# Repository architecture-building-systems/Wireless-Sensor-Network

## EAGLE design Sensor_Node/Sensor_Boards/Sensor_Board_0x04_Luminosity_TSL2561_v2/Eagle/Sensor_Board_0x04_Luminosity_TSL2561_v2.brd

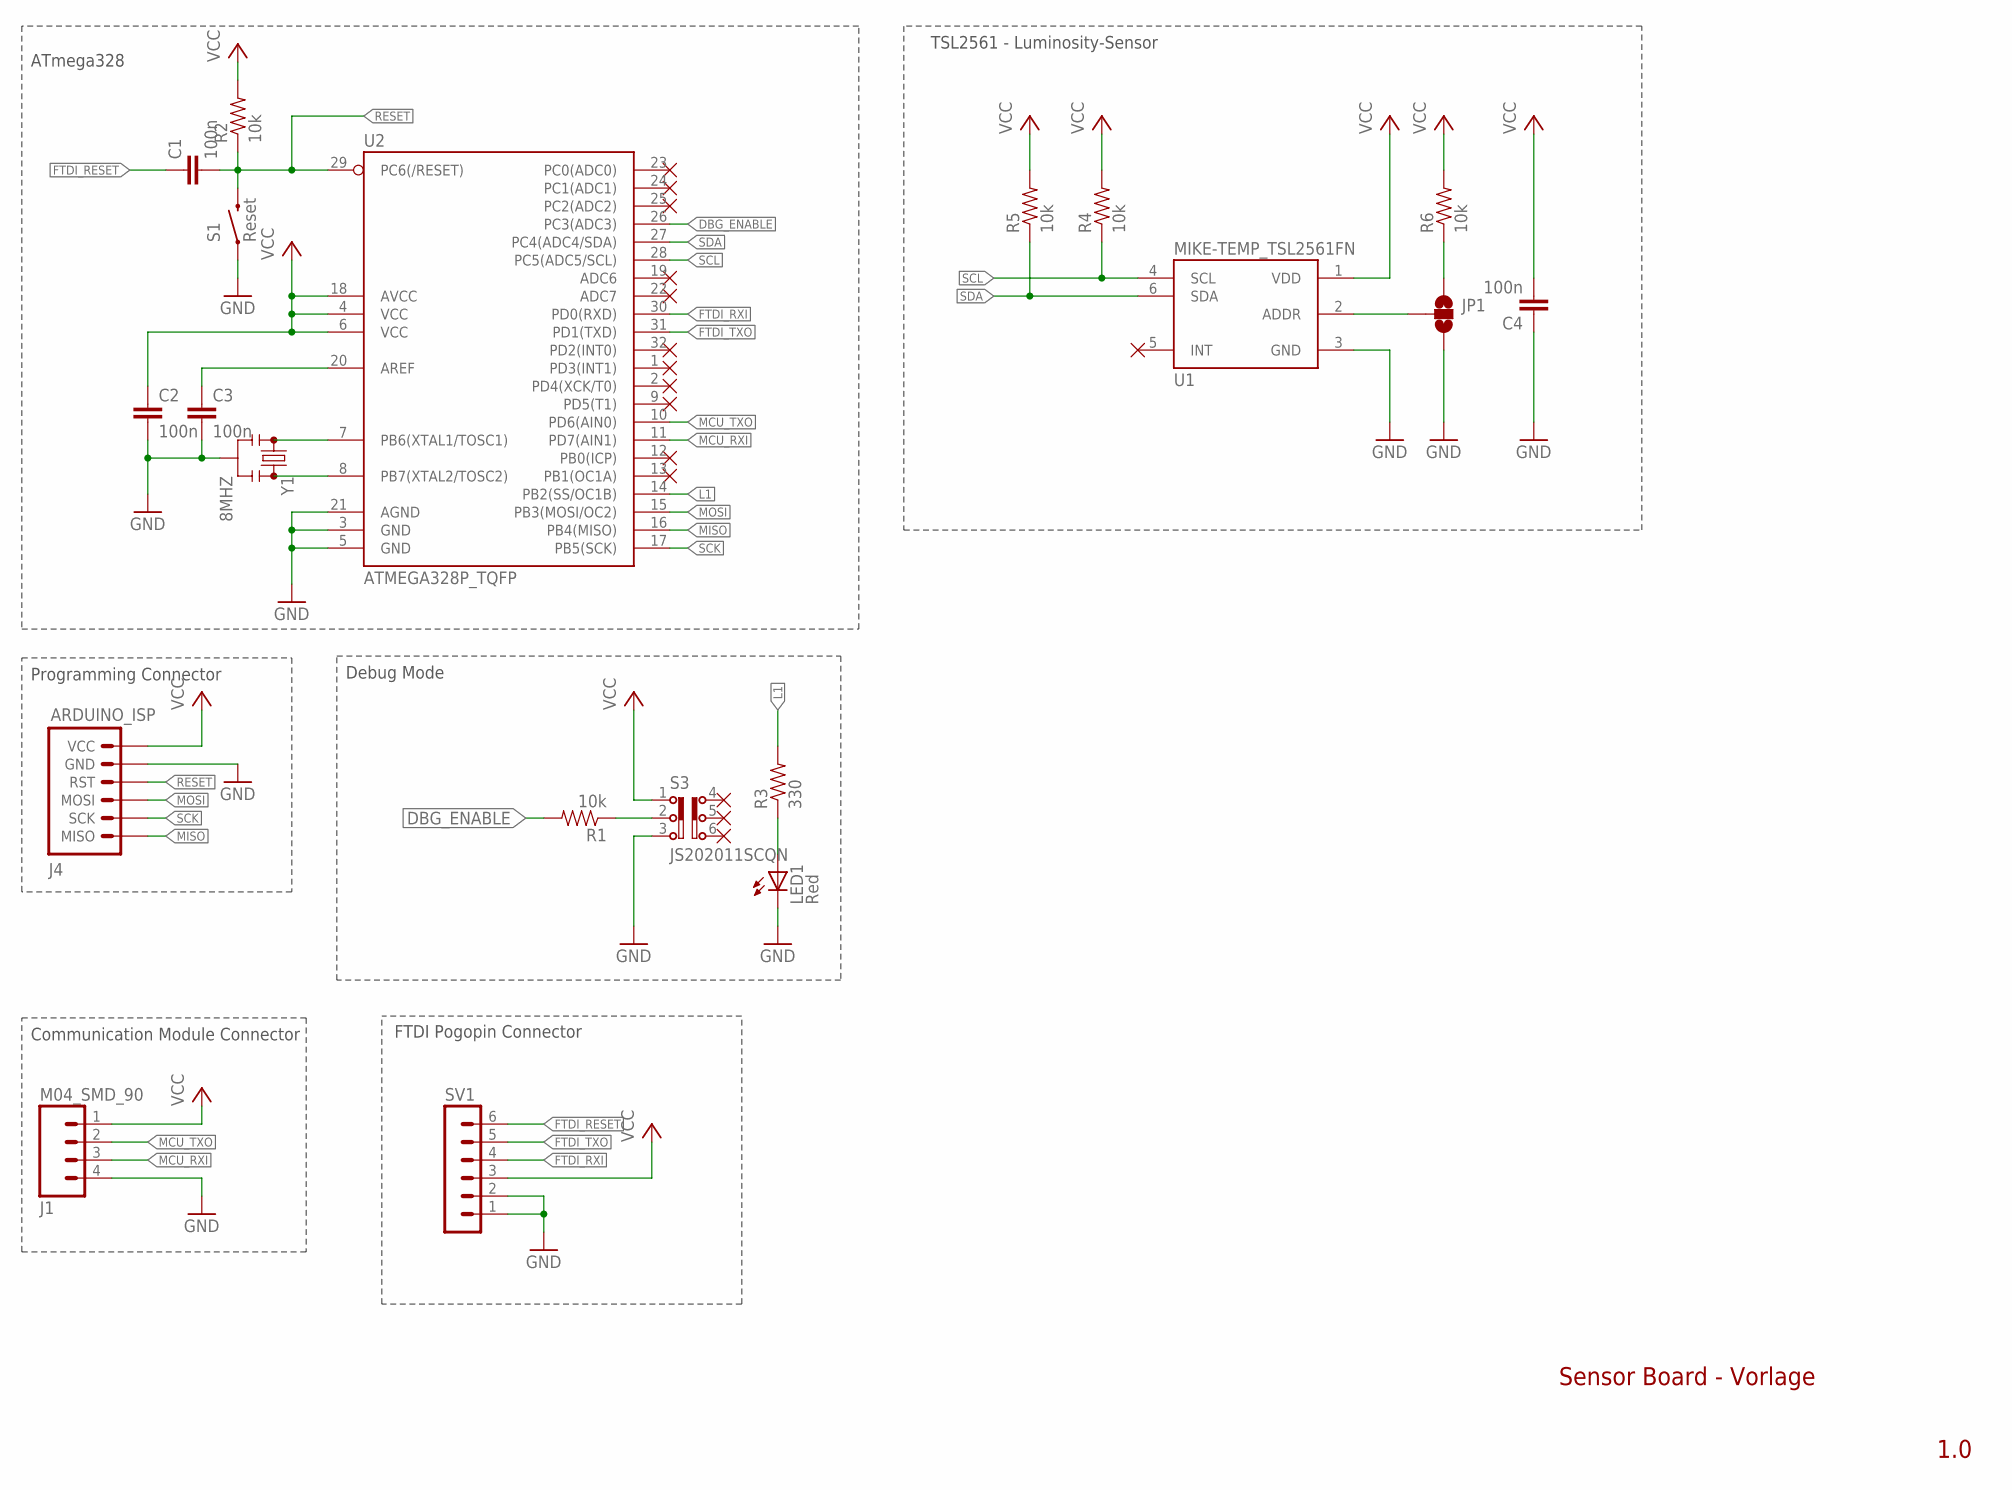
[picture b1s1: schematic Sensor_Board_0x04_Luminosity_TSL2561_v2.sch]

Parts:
C1, C2, C3, C4: 100n; C0805
J1: M04_SMD_90
J4: ARDUINO_ISP; M-2X3
JP1: MIKE-TEMP_SOLDERJUMPER_2WAYS; MIKE-TEMP_SJ_3
LED1: Red; SML0805
R1, R2, R4, R5, R6: 10k; 0805
R3: 330; 0805
S1: Reset; M-PUSHBUTTON-SMD
S3: JS202011SCQN
SV1: MA06-1
U1: MIKE-TEMP_TSL2561FN; MIKE-TEMP_FN-6
U2: ATMEGA328P_TQFP; TQFP32-08
Y1: 8MHZ; RESONATOR-SMD

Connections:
DBG_ENABLE: R1.2, U2.26 (PC3(ADC3))
FTDI_RESET: C1.1, SV1.6
FTDI_RXI: SV1.4, U2.30 (PD0(RXD))
FTDI_TXO: SV1.5, U2.31 (PD1(TXD))
GND: C2.2, C3.2, C4.1, J1.4, J4.P$5 (GND), JP1.3, LED1.C, S1.1 (LEFT), S1.2 (LEFT), S3.3, SV1.1, SV1.2, U1.3 (GND), U2.3 (GND), U2.5 (GND), U2.21 (AGND), Y1.2
L1: R3.2, U2.14 (PB2(SS/OC1B))
MCU_RXI: J1.3, U2.11 (PD7(AIN1))
MCU_TXO: J1.2, U2.10 (PD6(AIN0))
MISO: J4.P$1 (MISO), U2.16 (PB4(MISO))
MOSI: J4.P$3 (MOSI), U2.15 (PB3(MOSI/OC2))
unnamed: U2.8 (PB7(XTAL2/TOSC2)), Y1.3
unnamed: U2.7 (PB6(XTAL1/TOSC1)), Y1.1
unnamed: R1.1, S3.2
unnamed: JP1.1, R6.1
unnamed: JP1.2, U1.2 (ADDR)
unnamed: C3.1, U2.20 (AREF)
unnamed: LED1.A, R3.1
RESET: C1.2, J4.P$4 (RST), R2.1, S1.3 (RIGHT), S1.4 (RIGHT), U2.29 (PC6(/RESET))
SCK: J4.P$2 (SCK), U2.17 (PB5(SCK))
SCL: R4.1, U1.4 (SCL), U2.28 (PC5(ADC5/SCL))
SDA: R5.1, U1.6 (SDA), U2.27 (PC4(ADC4/SDA))
VCC: C2.1, C4.2, J1.1, J4.P$6 (VCC), R2.2, R4.2, R5.2, R6.2, S3.1, SV1.3, U1.1 (VDD), U2.4 (VCC), U2.6 (VCC), U2.18 (AVCC)

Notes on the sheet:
Debug Mode
Programming Connector
ATmega328
Communication Module Connector
Sensor Board - Vorlage
1.0
FTDI Pogopin Connector
TSL2561 - Luminosity-Sensor

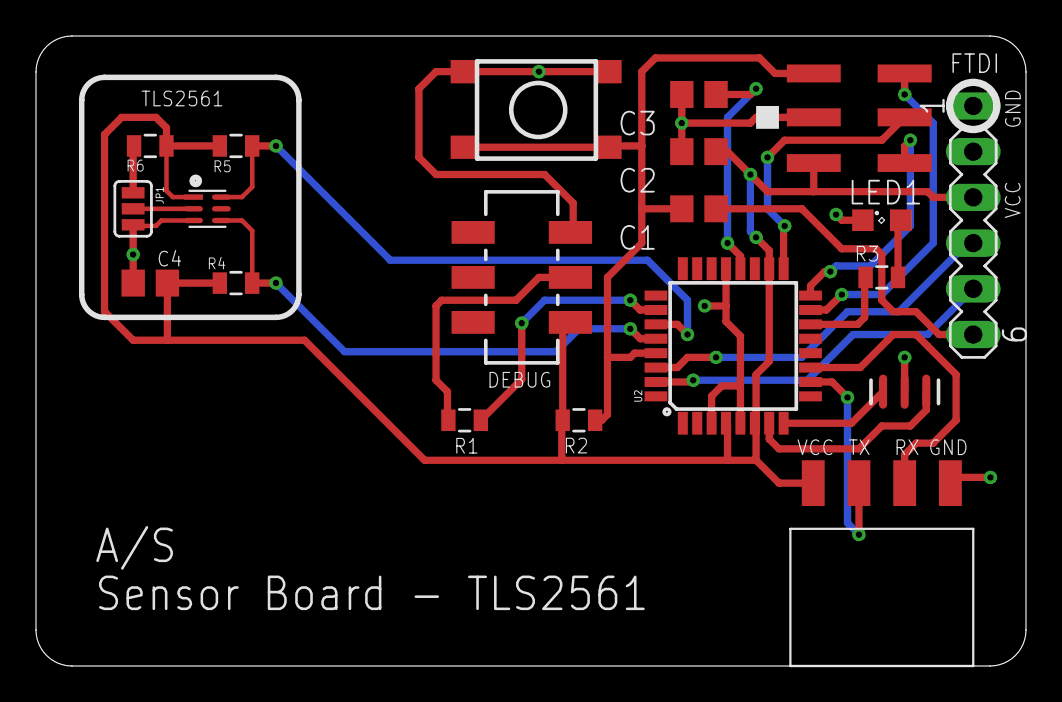
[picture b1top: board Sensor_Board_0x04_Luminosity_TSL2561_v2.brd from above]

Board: 2 copper layers, 55.0 x 35.0 mm, 20 parts (0 on the bottom side), 22 nets.

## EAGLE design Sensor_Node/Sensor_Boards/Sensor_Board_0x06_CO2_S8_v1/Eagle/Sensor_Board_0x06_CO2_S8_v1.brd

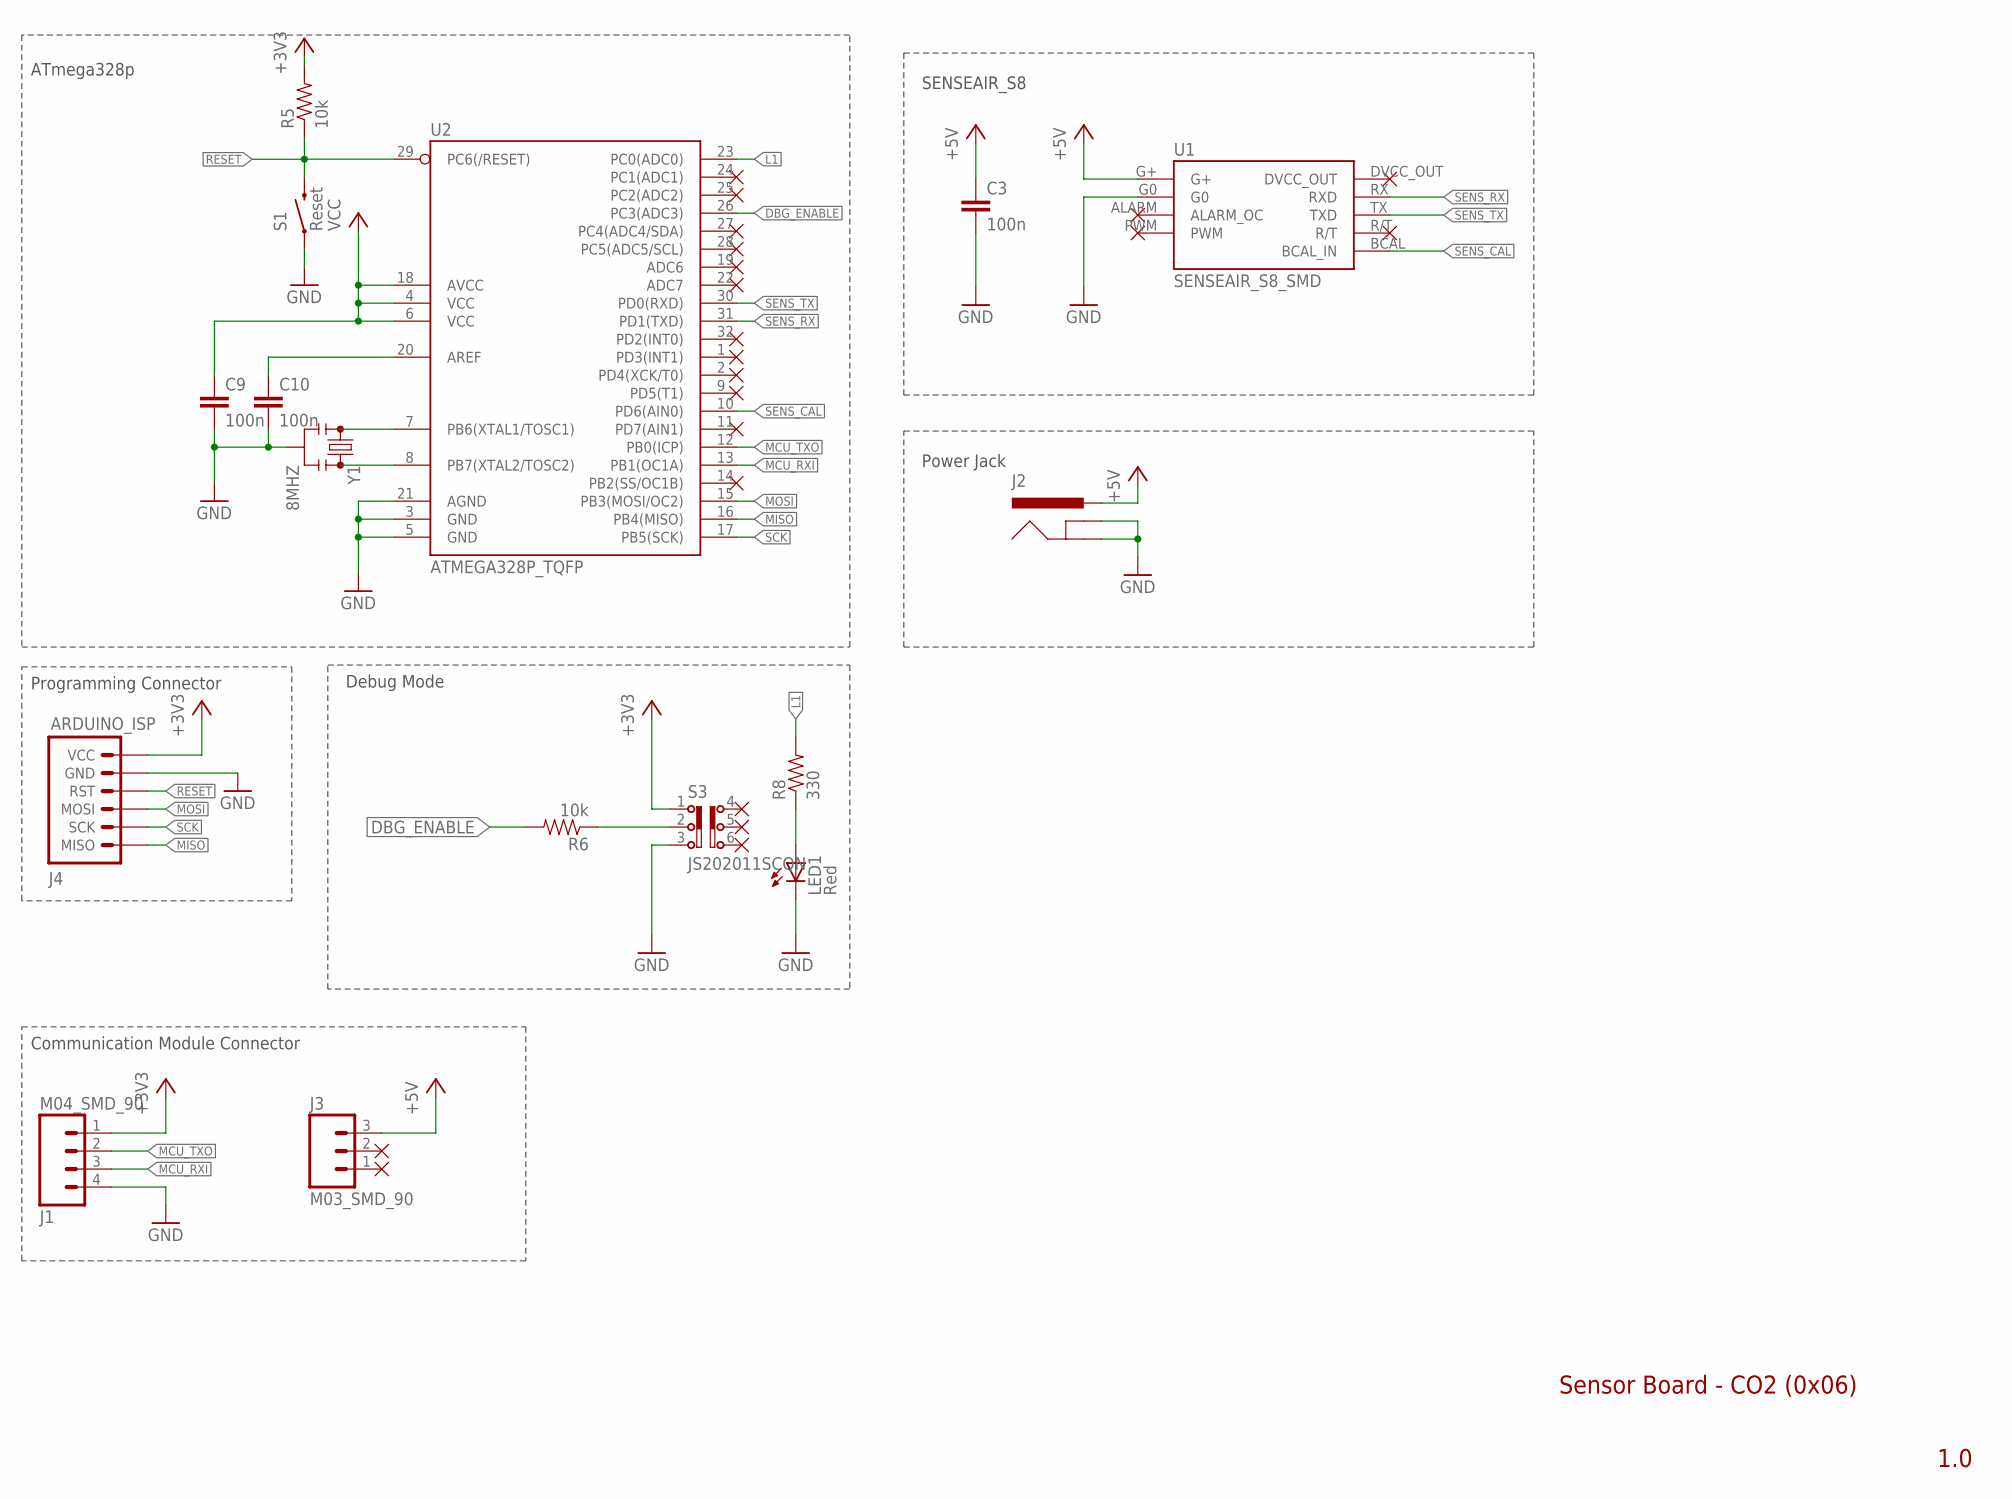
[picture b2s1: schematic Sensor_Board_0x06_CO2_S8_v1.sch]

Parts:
C3, C9, C10: 100n; C0805
J1: M04_SMD_90
J2: 5.5x2.1mm Barrel; POWER_JACK_SMD
J3: M03_SMD_90
J4: ARDUINO_ISP; M-2X3
LED1: Red; SML0805
R5, R6: 10k; 0805
R8: 330; 0805
S1: Reset; M-PUSHBUTTON-SMD
S3: JS202011SCQN
U1: SENSEAIR_S8_SMD
U2: ATMEGA328P_TQFP; TQFP32-08
Y1: 8MHZ; RESONATOR-SMD

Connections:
+3V3: C9.1, J1.1, J4.P$6 (VCC), R5.2, S3.1, U2.4 (VCC), U2.6 (VCC), U2.18 (AVCC)
+5V: C3.1, J2.VIN0 (PWR), J2.VIN1 (PWR), J3.3, U1.G+
DBG_ENABLE: R6.2, U2.26 (PC3(ADC3))
GND: C3.2, C9.2, C10.2, J1.4, J2.GND (GNDBREAK), J2.P$4 (GND), J4.P$5 (GND), LED1.C, S1.1 (LEFT), S1.2 (LEFT), S3.3, U1.G0, U2.3 (GND), U2.5 (GND), U2.21 (AGND), Y1.2
L1: R8.2, U2.23 (PC0(ADC0))
MCU_RXI: J1.3, U2.13 (PB1(OC1A))
MCU_TXO: J1.2, U2.12 (PB0(ICP))
MISO: J4.P$1 (MISO), U2.16 (PB4(MISO))
MOSI: J4.P$3 (MOSI), U2.15 (PB3(MOSI/OC2))
unnamed: U2.8 (PB7(XTAL2/TOSC2)), Y1.3
unnamed: U2.7 (PB6(XTAL1/TOSC1)), Y1.1
unnamed: R6.1, S3.2
unnamed: C10.1, U2.20 (AREF)
unnamed: LED1.A, R8.1
RESET: J4.P$4 (RST), R5.1, S1.3 (RIGHT), S1.4 (RIGHT), U2.29 (PC6(/RESET))
SCK: J4.P$2 (SCK), U2.17 (PB5(SCK))
SENS_CAL: U1.BCAL (BCAL_IN), U2.10 (PD6(AIN0))
SENS_RX: U1.RX (RXD), U2.31 (PD1(TXD))
SENS_TX: U1.TX (TXD), U2.30 (PD0(RXD))

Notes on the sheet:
Debug Mode
Programming Connector
ATmega328p
Communication Module Connector
SENSEAIR_S8
Sensor Board - CO2 (0x06)
1.0
Power Jack

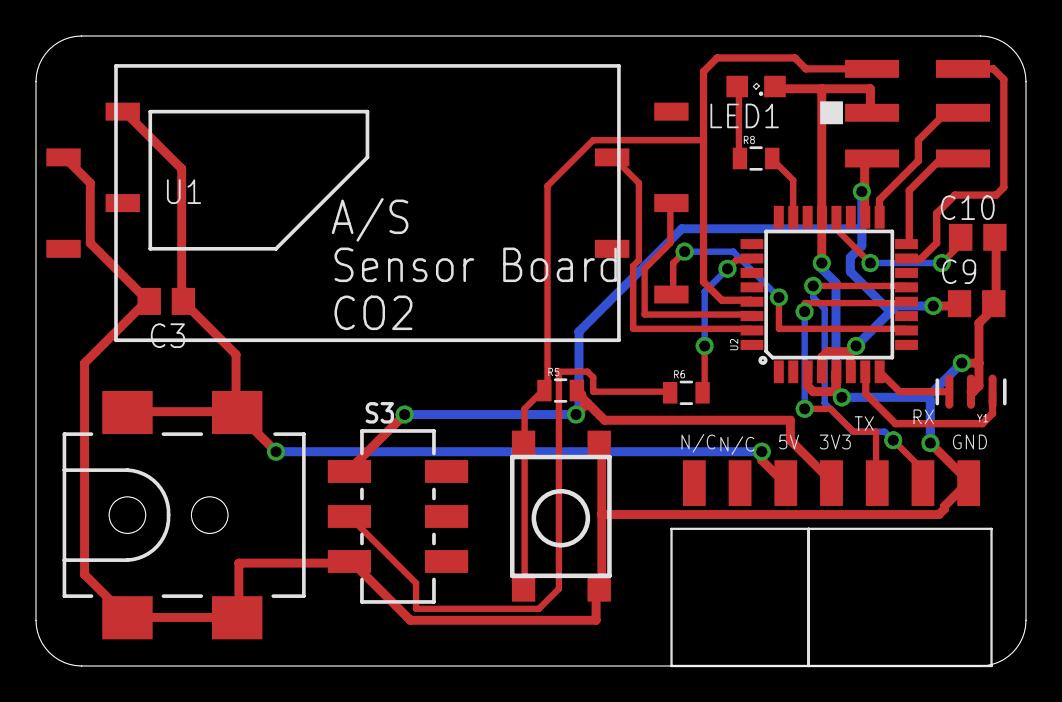
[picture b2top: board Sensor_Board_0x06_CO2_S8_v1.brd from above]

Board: 2 copper layers, 55.0 x 35.0 mm, 16 parts (0 on the bottom side), 19 nets.

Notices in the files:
parts and their libraries:
SparkFun-Passives: Licensing: Creative Commons ShareAlike 4.0 International - https://creativecommons.org/licenses/by-sa/4.0
